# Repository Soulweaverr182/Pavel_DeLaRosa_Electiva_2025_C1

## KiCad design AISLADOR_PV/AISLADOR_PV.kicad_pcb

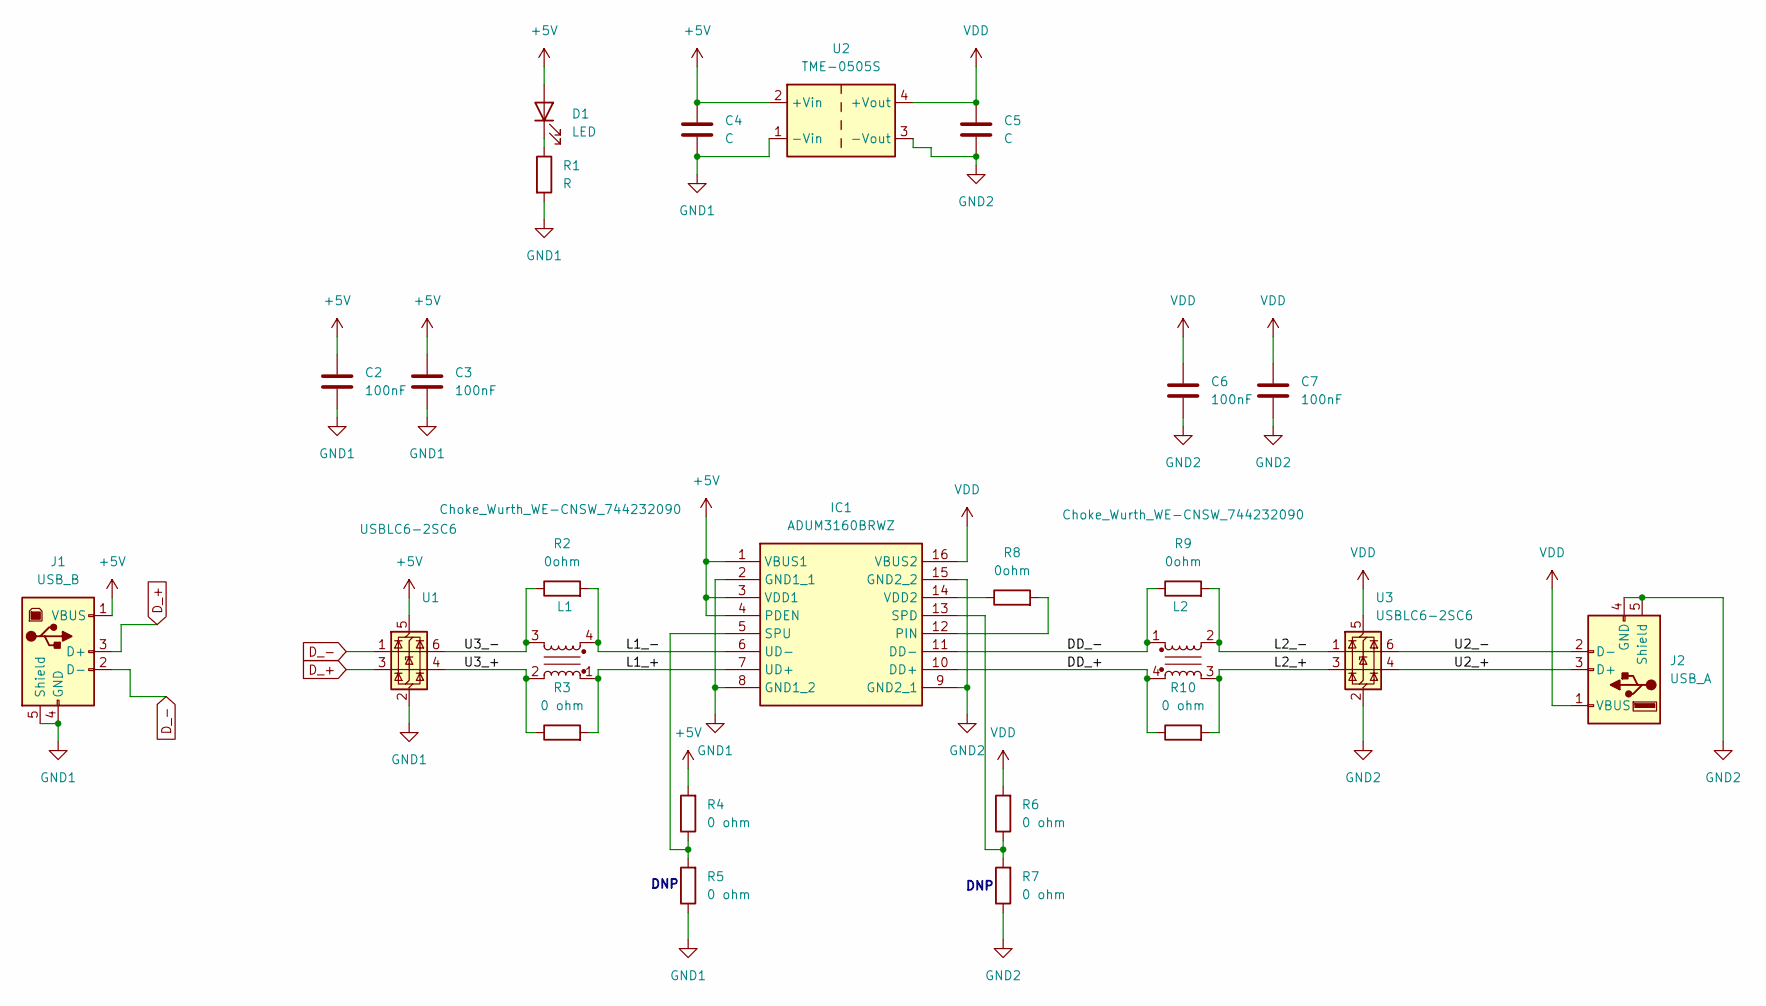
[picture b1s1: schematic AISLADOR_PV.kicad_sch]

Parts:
C2, C3, C6, C7: 100nF; C_0603_1608Metric
C4, C5: C; C_0603_1608Metric
D1: LED; LED_0402_1005Metric
IC1: ADUM3160BRWZ; SOIC127P1032X265-16N; Manufacturer_Part_Number ADUM3160BRWZ; Mouser Part Number 584-ADUM3160BRWZ
J1: USB_B; USB_B_Lumberg_2411_02_Horizontal
J2: USB_A; USB_A_Molex_67643_Horizontal
L1, L2: Choke_Wurth_WE-CNSW_744232090; L_CommonMode_Wurth_WE-CNSW-1206
R1: R; R_0402_1005Metric
R2, R8, R9: 0ohm; R_0603_1608Metric
R3, R4, R5, R6, R7, R10: 0 ohm; R_0603_1608Metric
U1, U3: USBLC6-2SC6; SOT-23-6
U2: TME-0505S; Converter_DCDC_TRACO_TME_03xxS_05xxS_12xxS_Single_THT

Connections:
+5V: C2.1, C3.1, C4.1, D1.2 (A), IC1.1 (VBUS1), IC1.3 (VDD1), IC1.4 (PDEN), J1.1 (VBUS), R4.2, U1.5 (VBUS), U2.2 (+Vin)
/DD_+: IC1.10 (DD+), L2.4, R10.1
/DD_-: IC1.11 (DD-), L2.1, R9.1
/L1_+: IC1.7 (UD+), L1.1, R3.2
/L1_-: IC1.6 (UD-), L1.4, R2.2
/L2_+: L2.3, R10.2, U3.3 (I/O2)
/L2_-: L2.2, R9.2, U3.1 (I/O1)
/U2_+: J2.3 (D+), U3.4 (I/O2)
/U2_-: J2.2 (D-), U3.6 (I/O1)
/U3_+: L1.2, R3.1, U1.4 (I/O2)
/U3_-: L1.3, R2.1, U1.6 (I/O1)
D_+: J1.3 (D+), U1.3 (I/O2)
D_-: J1.2 (D-), U1.1 (I/O1)
GND1: C2.2, C3.2, C4.2, IC1.2 (GND1_1), IC1.8 (GND1_2), J1.4 (GND), J1.5 (Shield), R1.2, R5.1, U1.2 (GND), U2.1 (-Vin)
GND2: C5.2, C6.2, C7.2, IC1.9 (GND2_1), IC1.15 (GND2_2), J2.4 (GND), J2.5 (Shield), R7.1, U2.3 (-Vout), U3.2 (GND)
unnamed: D1.1 (K), R1.1
unnamed: IC1.12 (PIN), R8.2
unnamed: IC1.13 (SPD), R6.1, R7.2
unnamed: IC1.5 (SPU), R4.1, R5.2
unnamed: IC1.14 (VDD2), R8.1
VDD: C5.1, C6.1, C7.1, IC1.16 (VBUS2), J2.1 (VBUS), R6.2, U2.4 (+Vout), U3.5 (VBUS)

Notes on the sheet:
DNP

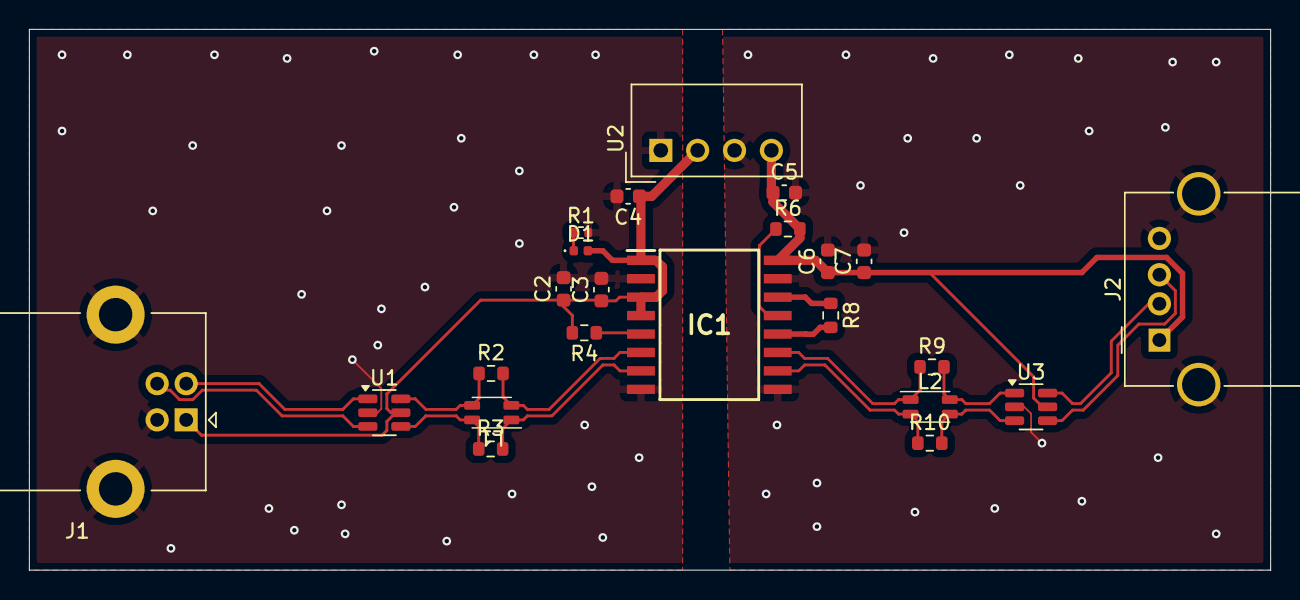
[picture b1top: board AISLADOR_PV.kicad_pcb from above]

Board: 2 copper layers, 85.5 x 37.2 mm, 23 parts (0 on the bottom side), 21 nets.

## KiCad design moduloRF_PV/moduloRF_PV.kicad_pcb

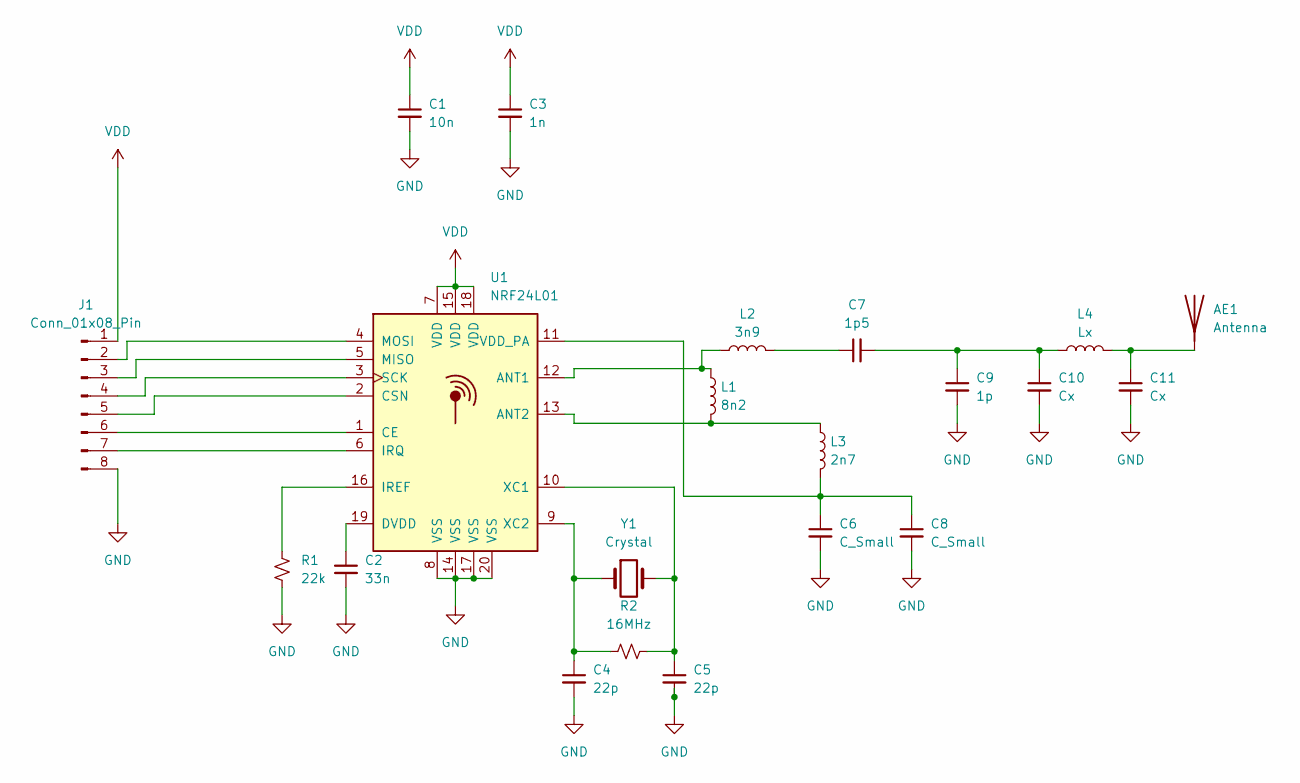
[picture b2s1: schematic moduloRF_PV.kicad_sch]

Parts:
AE1: Antenna; Texas_SWRA117D_2.4GHz_Right
C1: 10n; C_0201_0603Metric
C2: 33n; C_0402_1005Metric
C3: 1n; C_0402_1005Metric
C4, C5: 22p; C_0402_1005Metric
C6, C8: C_Small; C_0402_1005Metric
C7: 1p5; C_0402_1005Metric
C9: 1p; C_0402_1005Metric
C10, C11: Cx; C_0402_1005Metric
J1: Conn_01x08_Pin; Hirose_DF13-08P-1.25DSA_1x08_P1.25mm_Vertical
L1: 8n2; L_0402_1005Metric
L2: 3n9; L_0402_1005Metric
L3: 2n7; L_0402_1005Metric
L4: Lx; L_0402_1005Metric
R1: 22k; R_0402_1005Metric
R2: 16MHz; R_0402_1005Metric
U1: NRF24L01; QFN-20-1EP_4x4mm_P0.5mm_EP2.5x2.5mm
Y1: Crystal; Crystal_SMD_3215-2Pin_3.2x1.5mm

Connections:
GND: C1.2, C2.2, C3.2, C4.2, C5.2, C6.2, C8.2, C9.2, C10.2, C11.2, J1.8, R1.2, U1.8 (VSS), U1.14 (VSS), U1.17 (VSS), U1.20 (VSS), U1.21
unnamed: AE1.1 (A), C11.1, L4.2
unnamed: C7.1, L2.2
unnamed: C7.2, C9.1, C10.1, L4.1
unnamed: J1.2, U1.4 (MOSI)
unnamed: J1.3, U1.5 (MISO)
unnamed: J1.4, U1.3 (SCK)
unnamed: J1.5, U1.2 (CSN)
unnamed: J1.6, U1.1 (CE)
unnamed: J1.7, U1.6 (IRQ)
unnamed: L1.1, L2.1, U1.12 (ANT1)
unnamed: L1.2, L3.1, U1.13 (ANT2)
unnamed: C2.1, U1.19 (DVDD)
unnamed: R1.1, U1.16 (IREF)
unnamed: C6.1, C8.1, L3.2, U1.11 (VDD_PA)
unnamed: C5.1, R2.2, U1.10 (XC1), Y1.2
unnamed: C4.1, R2.1, U1.9 (XC2), Y1.1
VDD: C1.1, C3.1, J1.1, U1.7 (VDD), U1.15 (VDD), U1.18 (VDD)

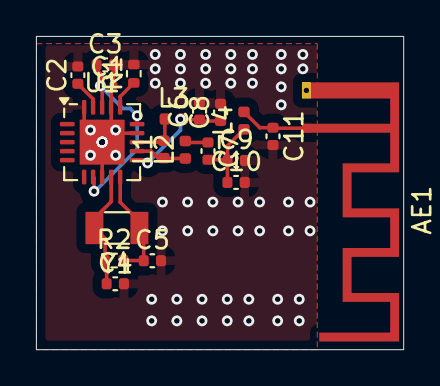
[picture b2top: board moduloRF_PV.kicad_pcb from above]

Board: 2 copper layers, 20.4 x 17.4 mm, 20 parts (0 on the bottom side), 12 nets.

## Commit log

2025-01-24 mi primer commit
2025-01-24 Ahora el index html tiene codigo html
2025-01-24 he agregado un .gitignore
2025-04-25 Hoja de projecto
2025-04-25 piezas y hoja de projecto
2025-04-25 movi hoja en folder
2025-04-25 agregando Aislador
2025-04-25 Agregando hoja de projecto
2025-04-25 Organinzano hoja de projecto
2025-04-25 Piezas en freecad
2025-04-25 Pieza en freecad
2025-04-25 Add files via upload
    PDF de pieza
